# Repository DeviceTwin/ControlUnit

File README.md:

# LEDControl_HW

:one: This is my first PCB design what I ordered from real PCB factory.<br>
:two: Also this is my first PCB what I soldering using reflow owen.

Hardware of LED control unit based on:<br>
<a href="https://www.youtube.com/watch?v=kcwvuwetgEQ"
			target="_blank">Hardware Design with the RP2040: Custom PCB Based on the Raspberry Pi Pico | Digi-Key Electronics</a>

PCB design help:<br>
<a href="https://www.youtube.com/watch?v=ge6gYIENo8Q"
			target="_blank">How to Make a Raspberry Pi Compute Module 4 Carrier Board in KiCad - Part 2 | Digi-Key Electronics</a>

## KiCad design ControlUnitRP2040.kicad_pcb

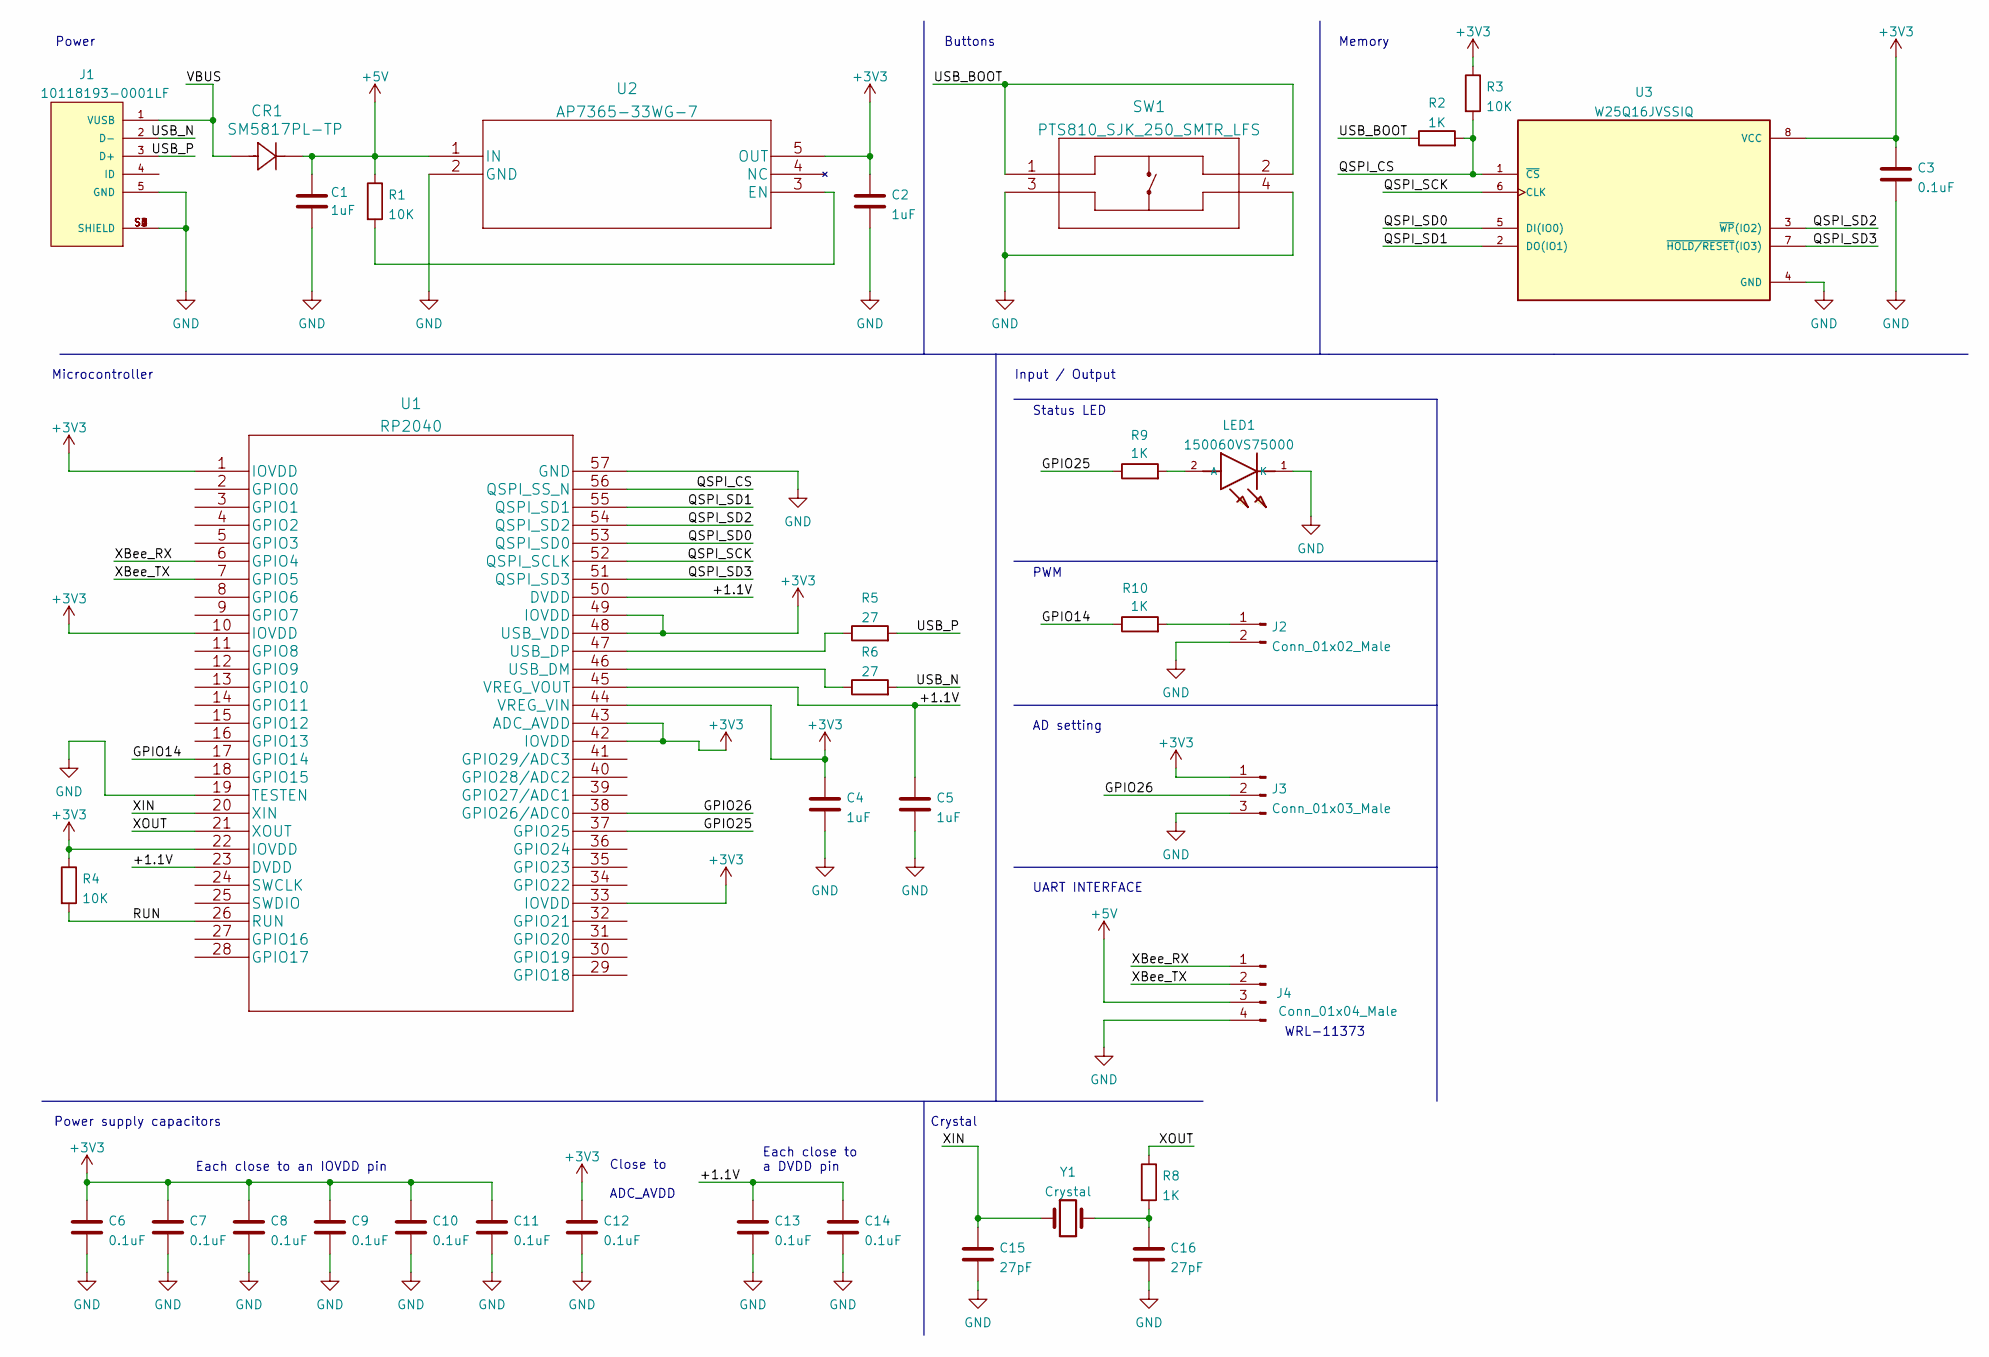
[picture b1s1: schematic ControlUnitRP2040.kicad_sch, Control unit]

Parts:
C1, C2, C4, C5: 1uF; C_0603_1608Metric_Pad1.08x0.95mm_HandSolder; Digikey 311-1445-1-ND
C3, C6, C7, C8, C9, C10, C11, C12, C13, C14: 0.1uF; C_0603_1608Metric_Pad1.08x0.95mm_HandSolder; Digikey 587-1245-1-ND
C15, C16: 27pF; C_0603_1608Metric_Pad1.08x0.95mm_HandSolder; Digikey 399-C0603C270F3HACAUTOCT-ND
CR1: SM5817PL-TP; Digikey SM5817PL-TPMSCT-ND
J1: 10118193-0001LF; FCI_10118193-0001LF; Digikey 609-4616-1-ND
J2: Conn_01x02_Male; PinHeader_1x02_P2.54mm_Vertical; Digikey 2057-PH1-02-UA-ND
J3: Conn_01x03_Male; PinHeader_1x03_P2.54mm_Vertical; Digikey 2057-PH1-03-UA-ND
J4: Conn_01x04_Male; PinHeader_1x04_P2.54mm_Vertical; Digikey 2057-PH1-04-UA-ND
LED1: 150060VS75000; LEDC1608X80N; Digikey 732-4980-1-ND
R1, R3, R4: 10K; R_0603_1608Metric_Pad0.98x0.95mm_HandSolder; Digikey 13-AC0603DR-0710KLCT-ND
R2, R8, R9, R10: 1K; R_0603_1608Metric_Pad0.98x0.95mm_HandSolder; Digikey P20283CT-ND
R5, R6: 27; R_0603_1608Metric_Pad0.98x0.95mm_HandSolder; Digikey 311-27.0HRCT-ND
SW1: PTS810_SJK_250_SMTR_LFS; PTS810 SJK 250 SMTR LFS; Digikey CKN10503CT-ND
U1: RP2040; Digikey 2648-SC0914(7)CT-ND
U2: AP7365-33WG-7; Digikey AP7365-33WG-7DICT-ND
U3: W25Q16JVSSIQ; SOIC127P790X216-8N; Digikey W25Q16JVSSIQ-ND
Y1: Crystal; ABLS-12.000MHZ-B4-T; Digikey 535-10218-1-ND

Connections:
+3V3: C2.1, C3.1, C4.1, C6.1, C7.1, C8.1, C9.1, C10.1, C11.1, C12.1, J3.1, R3.1, R4.1, U1.1 (IOVDD), U1.10 (IOVDD), U1.22 (IOVDD), U1.33 (IOVDD), U1.42 (IOVDD), U1.43 (ADC_AVDD), U1.44 (VREG_VIN), U1.48 (USB_VDD), U1.49 (IOVDD), U2.5 (OUT), U3.8 (VCC)
+5V: C1.1, CR1.1, J4.3, R1.1, U2.1 (IN)
/+1.1V: C5.1, C13.1, C14.1, U1.23 (DVDD), U1.45 (VREG_VOUT), U1.50 (DVDD)
/GPIO14: R10.1, U1.17 (GPIO14)
/GPIO25: R9.1, U1.37 (GPIO25)
/GPIO26: J3.2, U1.38 (GPIO26/ADC0)
/QSPI_CS: R2.2, R3.2, U1.56 (QSPI_SS_N), U3.1 (~CS)
/QSPI_SCK: U1.52 (QSPI_SCLK), U3.6 (CLK)
/QSPI_SD0: U1.53 (QSPI_SD0), U3.5 (DI(IO0))
/QSPI_SD1: U1.55 (QSPI_SD1), U3.2 (DO(IO1))
/QSPI_SD2: U1.54 (QSPI_SD2), U3.3 (~WP(IO2))
/QSPI_SD3: U1.51 (QSPI_SD3), U3.7 (~HOLD/RESET(IO3))
/RUN: R4.2, U1.26 (RUN)
/USB_BOOT: R2.1, SW1.1, SW1.2
/USB_N: J1.2 (D-), R6.2
/USB_P: J1.3 (D+), R5.2
/VBUS: CR1.2, J1.1 (VUSB)
/XBee_RX: J4.1, U1.6 (GPIO4)
/XBee_TX: J4.2, U1.7 (GPIO5)
/XIN: C15.1, U1.20 (XIN), Y1.1
/XOUT: R8.1, U1.21 (XOUT)
GND: C1.2, C2.2, C3.2, C4.2, C5.2, C6.2, C7.2, C8.2, C9.2, C10.2, C11.2, C12.2, C13.2, C14.2, C15.2, C16.2, J1.5 (GND), J1.S1 (SHIELD), J1.S2 (SHIELD), J1.S3 (SHIELD), J1.S4 (SHIELD), J1.S5 (SHIELD), J1.S6 (SHIELD), J2.2, J3.3, J4.4, LED1.1 (K), SW1.3, SW1.4, U1.19 (TESTEN), U1.57 (GND), U2.2 (GND), U3.4 (GND)
unnamed: C16.1, R8.2, Y1.2
unnamed: J2.1, R10.2
unnamed: LED1.2 (A), R9.2
unnamed: R1.2, U2.3 (EN)
unnamed: R5.1, U1.47 (USB_DP)
unnamed: R6.1, U1.46 (USB_DM)

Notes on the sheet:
Power supply capacitors
Buttons
Memory
PWM
Power
Status LED
Each close to an IOVDD pin
WRL-11373
Input / Output
Close to ADC_AVDD
Microcontroller
AD setting
Crystal
Each close to a DVDD pin
UART INTERFACE

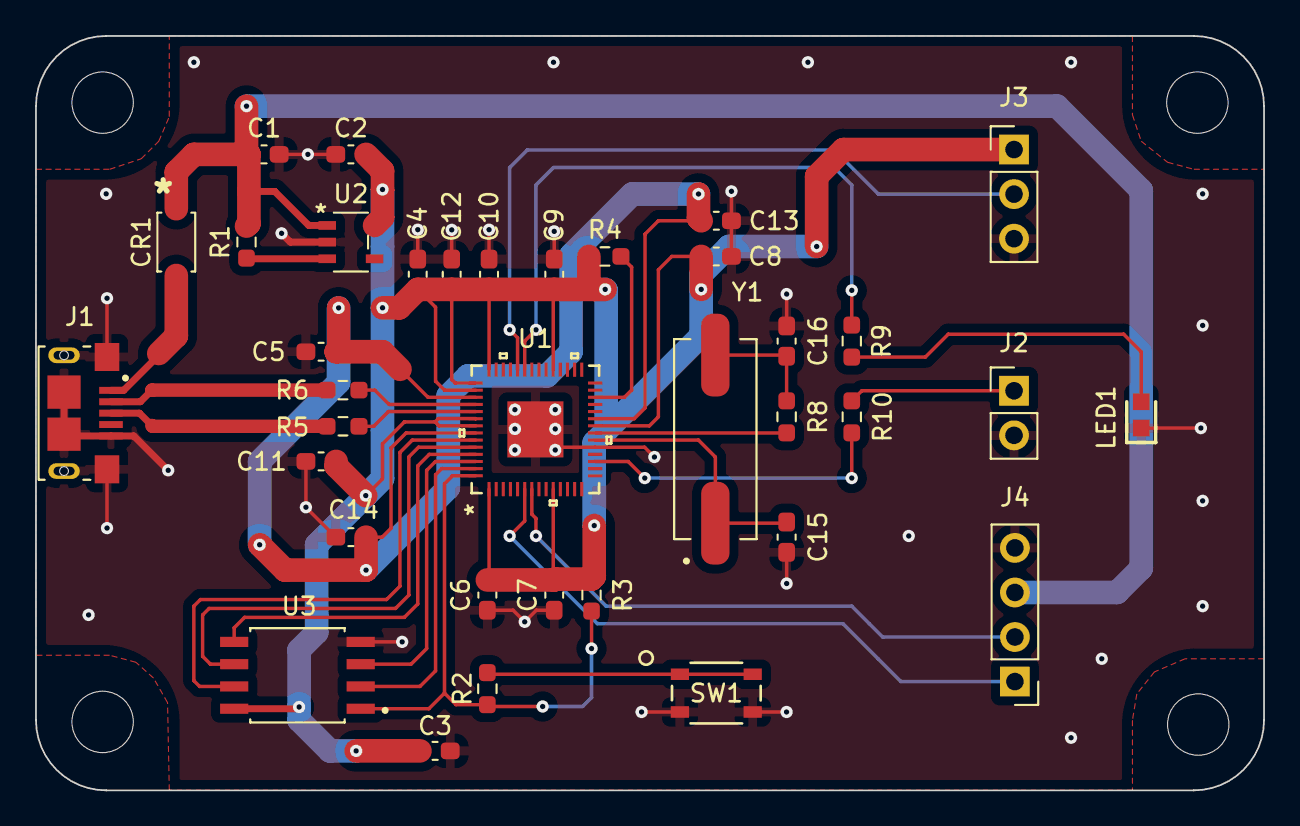
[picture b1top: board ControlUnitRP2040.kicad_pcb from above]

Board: 2 copper layers, 70.0 x 43.0 mm, 40 parts (0 on the bottom side), 28 nets.

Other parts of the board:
REF1, REF2, REF3, REF4: MountingHole_3.5mm

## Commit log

2022-04-22 Version 1.0
2022-05-18 Changed HW
2022-09-14 Text updated
2022-11-29 Text changed.
2022-12-04 Added PCB design help
2022-12-04 ControlUnit is now LEDControl

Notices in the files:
parts and their libraries:
Copyright 2016 Accelerated Designs. All rights reserved.
Copyright 2021 Accelerated Designs. All rights reserved.
